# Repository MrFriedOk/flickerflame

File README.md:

# flickerflame
## What

## Why

## References
- [Cloveian](https://github.com/Cloveian)
- ["void_switch"](https://github.com/riskable/void_switch)
- [crkbd](https://github.com/foostan/crkbd)
- [SK9822 symbols/footprints](https://github.com/Crafty-The-Fox/SK9822-EC20-Kicad/tree/main)

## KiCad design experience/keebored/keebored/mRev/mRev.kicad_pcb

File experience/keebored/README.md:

# Keebored (idk what to name it)
## Objective
My goal with this project is to familiarize myself with KiCAD and other CAD-ing tools so I can move towards building a mouse. Not only that, but I can *maybe* get a functional keyboard sort of thing to use to play osu! or something.
## Overview, the idea
A small, semi-portable USB C keyboard.
### Key Features
- 128x64 OLED display via I2C
- Analog HE switches, directly to MCU ADC (hall effect)
- RGB per key
- 1khz (ceiling due to USB restrictions without PHY)
- Rotary encoder
~~- ~55mm wide, ~95mm tall~~
## [Design](./design/README.md)

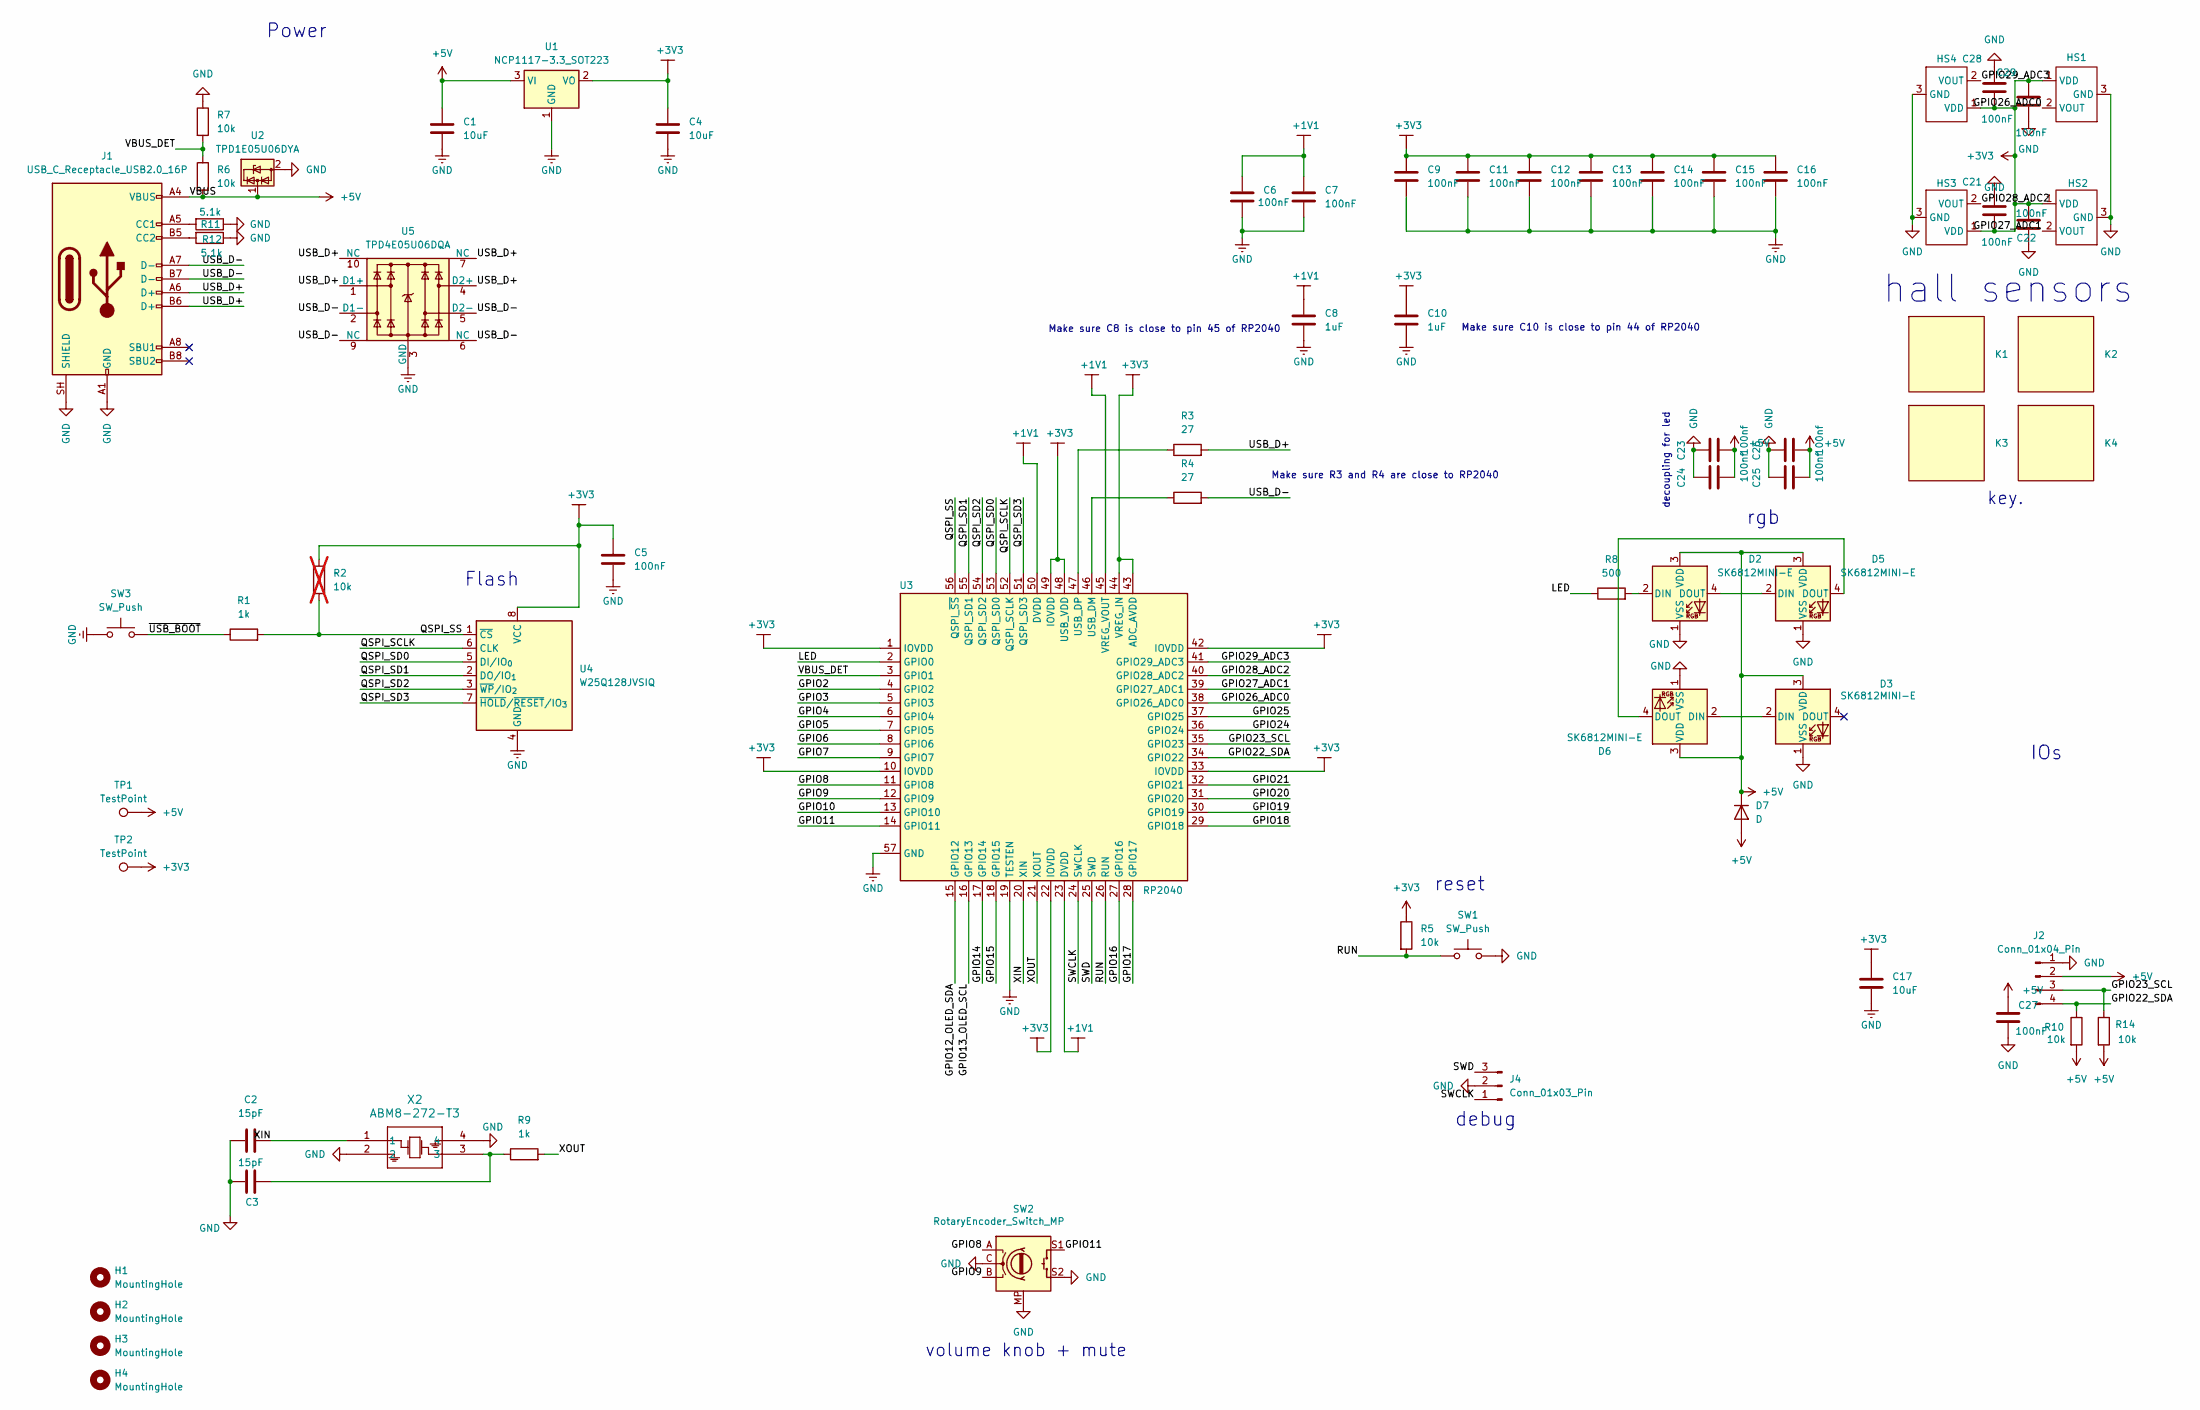
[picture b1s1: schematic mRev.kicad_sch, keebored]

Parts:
C1, C4, C17: 10uF; C_0805_2012Metric
C2, C3: 15pF; C_0402_1005Metric
C5, C6, C7, C9, C11, C12, C13, C14, C15, C16, C21, C22, C27, C28, C29: 100nF; C_0402_1005Metric
C8, C10: 1uF; C_0402_1005Metric
C23, C24, C25, C26: 100nf; C_0402_1005Metric
D2, D3, D5, D6: SK6812MINI-E; LED_SK6812MINI-E_3.2x2.8mm_P1.5mm_ReverseMount
D7: D; D_0402_1005Metric
H1, H2, H3, H4: MountingHole; MountingHole_3mm
HS1, HS2, HS3, HS4: SOT-23-3
J1: USB_C_Receptacle_USB2.0_16P; USB_C_Receptacle_HCTL_HC-TYPE-C-16P-01A
J2: Conn_01x04_Pin; JST_XH_S4B-XH-A-1_1x04_P2.50mm_Horizontal
J4: Conn_01x03_Pin; JST_XH_S3B-XH-A-1_1x03_P2.50mm_Horizontal
K1, K2, K3, K4: HE_Switch_Socket
R1, R9: 1k; R_0402_1005Metric
R2: 10k; R_0402_1005Metric; not fitted
R3, R4: 27; R_0402_1005Metric
R5, R6, R7, R10, R14: 10k; R_0402_1005Metric
R8: 500; R_0402_1005Metric
R11, R12: 5.1k; R_0402_1005Metric
SW1, SW3: SW_Push; SW_PUSH_1P1T_6x3.5mm_H4.3_APEM_MJTP1243
SW2: RotaryEncoder_Switch_MP; RotaryEncoder_Alps_EC11E-Switch_Vertical_H20mm
TP1, TP2: TestPoint; TestPoint_Pad_D1.0mm
U1: NCP1117-3.3_SOT223; SOT-223-3_TabPin2
U2: TPD1E05U06DYA; D_SOD-523
U3: RP2040; QFN-56-1EP_7x7mm_P0.4mm_EP3.2x3.2mm; part_uid RP-01EKHS-ZTKTEH
U4: W25Q128JVSIQ; SOIC-8_5.3x5.3mm_P1.27mm; JLCPCB Part # C113767
U5: TPD4E05U06DQA; USON-10_2.5x1.0mm_P0.5mm
X2: ABM8-272-T3; ABM8-272-T3_ABR

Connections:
+1V1: C6.1, C7.1, C8.1, U3.23 (DVDD), U3.45 (VREG_VOUT), U3.50 (DVDD)
+3V3: C4.1, C5.1, C9.1, C10.1, C11.1, C12.1, C13.1, C14.1, C15.1, C16.1, C17.1, C21.1, C22.1, C28.1, C29.2, HS1.1 (VDD), HS2.1 (VDD), HS3.1 (VDD), HS4.1 (VDD), R2.1, R5.1, TP2.1 (1_1), U1.2 (VO), U3.1 (IOVDD), U3.10 (IOVDD), U3.22 (IOVDD), U3.33 (IOVDD), U3.42 (IOVDD), U3.43 (ADC_AVDD), U3.44 (VREG_IN), U3.48 (USB_VDD), U3.49 (IOVDD), U4.8 (VCC)
+5V: C1.1, C23.2, C24.2, C25.2, C26.2, C27.1, D2.3 (VDD), D3.3 (VDD), D5.3 (VDD), D6.3 (VDD), D7.1 (K), D7.2 (A), J1.A4 (VBUS), J1.A9 (VBUS), J1.B4 (VBUS), J1.B9 (VBUS), J2.2, R6.2, R10.2, R14.2, TP1.1 (1_1), U1.3 (VI), U2.1 (I/O)
/GPIO2: U3.4 (GPIO2)
/GPIO3: U3.5 (GPIO3)
/GPIO4: U3.6 (GPIO4)
/GPIO5: U3.7 (GPIO5)
/GPIO6: U3.8 (GPIO6)
/GPIO7: U3.9 (GPIO7)
/GPIO8: SW2.A, U3.11 (GPIO8)
/GPIO9: SW2.B, U3.12 (GPIO9)
/GPIO10: U3.13 (GPIO10)
/GPIO11: SW2.S1, U3.14 (GPIO11)
/GPIO12_OLED_SDA: U3.15 (GPIO12)
/GPIO13_OLED_SCL: U3.16 (GPIO13)
/GPIO14: U3.17 (GPIO14)
/GPIO15: U3.18 (GPIO15)
/GPIO16: U3.27 (GPIO16)
/GPIO17: U3.28 (GPIO17)
/GPIO18: U3.29 (GPIO18)
/GPIO19: U3.30 (GPIO19)
/GPIO20: U3.31 (GPIO20)
/GPIO21: U3.32 (GPIO21)
/GPIO22_SDA: J2.4, R10.1, U3.34 (GPIO22)
/GPIO23_SCL: J2.3, R14.1, U3.35 (GPIO23)
/GPIO24: U3.36 (GPIO24)
/GPIO25: U3.37 (GPIO25)
/GPIO26_ADC0: HS1.2 (VOUT), U3.38 (GPIO26_ADC0)
/GPIO27_ADC1: HS2.2 (VOUT), U3.39 (GPIO27_ADC1)
/GPIO28_ADC2: HS3.2 (VOUT), U3.40 (GPIO28_ADC2)
/GPIO29_ADC3: HS4.2 (VOUT), U3.41 (GPIO29_ADC3)
/LED: R8.1, U3.2 (GPIO0)
/QSPI_SCLK: U3.52 (QSPI_SCLK), U4.6 (CLK)
/QSPI_SD0: U3.53 (QSPI_SD0), U4.5 (DI/IO_{0})
/QSPI_SD1: U3.55 (QSPI_SD1), U4.2 (DO/IO_{1})
/QSPI_SD2: U3.54 (QSPI_SD2), U4.3 (~WP/IO_{2})
/QSPI_SD3: U3.51 (QSPI_SD3), U4.7 (~HOLD/~RESET/IO_{3})
/QSPI_SS: R1.2, R2.2, U3.56 (QSPI_~SS), U4.1 (~CS)
/RUN: R5.2, SW1.1, U3.26 (RUN)
/SWCLK: J4.1, U3.24 (SWCLK)
/SWD: J4.3, U3.25 (SWD)
/USB_D+: J1.A6 (D+), J1.B6 (D+), R3.2, U5.1 (D1+), U5.4 (D2+), U5.7 (NC), U5.10 (NC)
/USB_D-: J1.A7 (D-), J1.B7 (D-), R4.2, U5.2 (D1-), U5.5 (D2-), U5.6 (NC), U5.9 (NC)
/VBUS_DET: R6.1, R7.2, U3.3 (GPIO1)
/XIN: C2.2, U3.20 (XIN), X2.1
/XOUT: R9.2, U3.21 (XOUT)
/~USB_BOOT: R1.1, SW3.2
GND: C1.2, C2.1, C3.1, C4.2, C5.2, C6.2, C7.2, C8.2, C9.2, C10.2, C11.2, C12.2, C13.2, C14.2, C15.2, C16.2, C17.2, C21.2, C22.2, C23.1, C24.1, C25.1, C26.1, C27.2, C28.2, C29.1, D2.1 (VSS), D3.1 (VSS), D5.1 (VSS), D6.1 (VSS), HS1.3 (GND), HS2.3 (GND), HS3.3 (GND), HS4.3 (GND), J1.A1 (GND), J1.A12 (GND), J1.B1 (GND), J1.B12 (GND), J1.SH (SHIELD), J2.1, J4.2, R7.1, R11.1, R12.1, SW1.2, SW2.C, SW2.MP, SW2.S2, SW3.1, U1.1 (GND), U2.2 (GND), U3.19 (TESTEN), U3.57 (GND), U4.4 (GND), U5.3 (GND), U5.8 (GND), X2.2, X2.4
unnamed: C3.2, R9.1, X2.3
unnamed: D2.2 (DIN), R8.2
unnamed: D2.4 (DOUT), D5.2 (DIN)
unnamed: D3.2 (DIN), D6.2 (DIN)
unnamed: D5.4 (DOUT), D6.4 (DOUT)
unnamed: J1.A5 (CC1), R11.2
unnamed: J1.B5 (CC2), R12.2
unnamed: R4.1, U3.46 (USB_DM)
unnamed: R3.1, U3.47 (USB_DP)

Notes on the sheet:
volume knob + mute
rgb
Power
hall sensors
Flash
reset
IOs
Make sure C10 is close to pin 44 of RP2040
Make sure C8 is close to pin 45 of RP2040
Make sure R3 and R4 are close to RP2040
key.
decoupling for led
debug

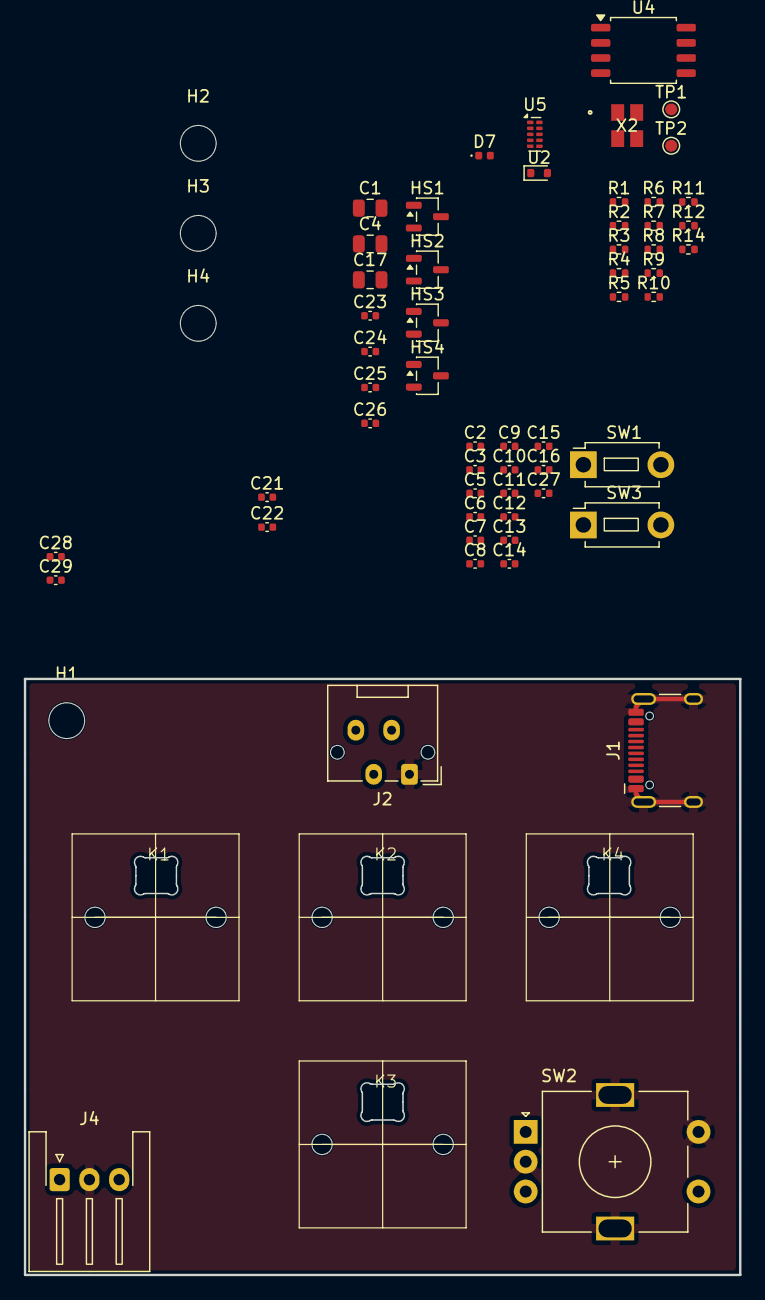
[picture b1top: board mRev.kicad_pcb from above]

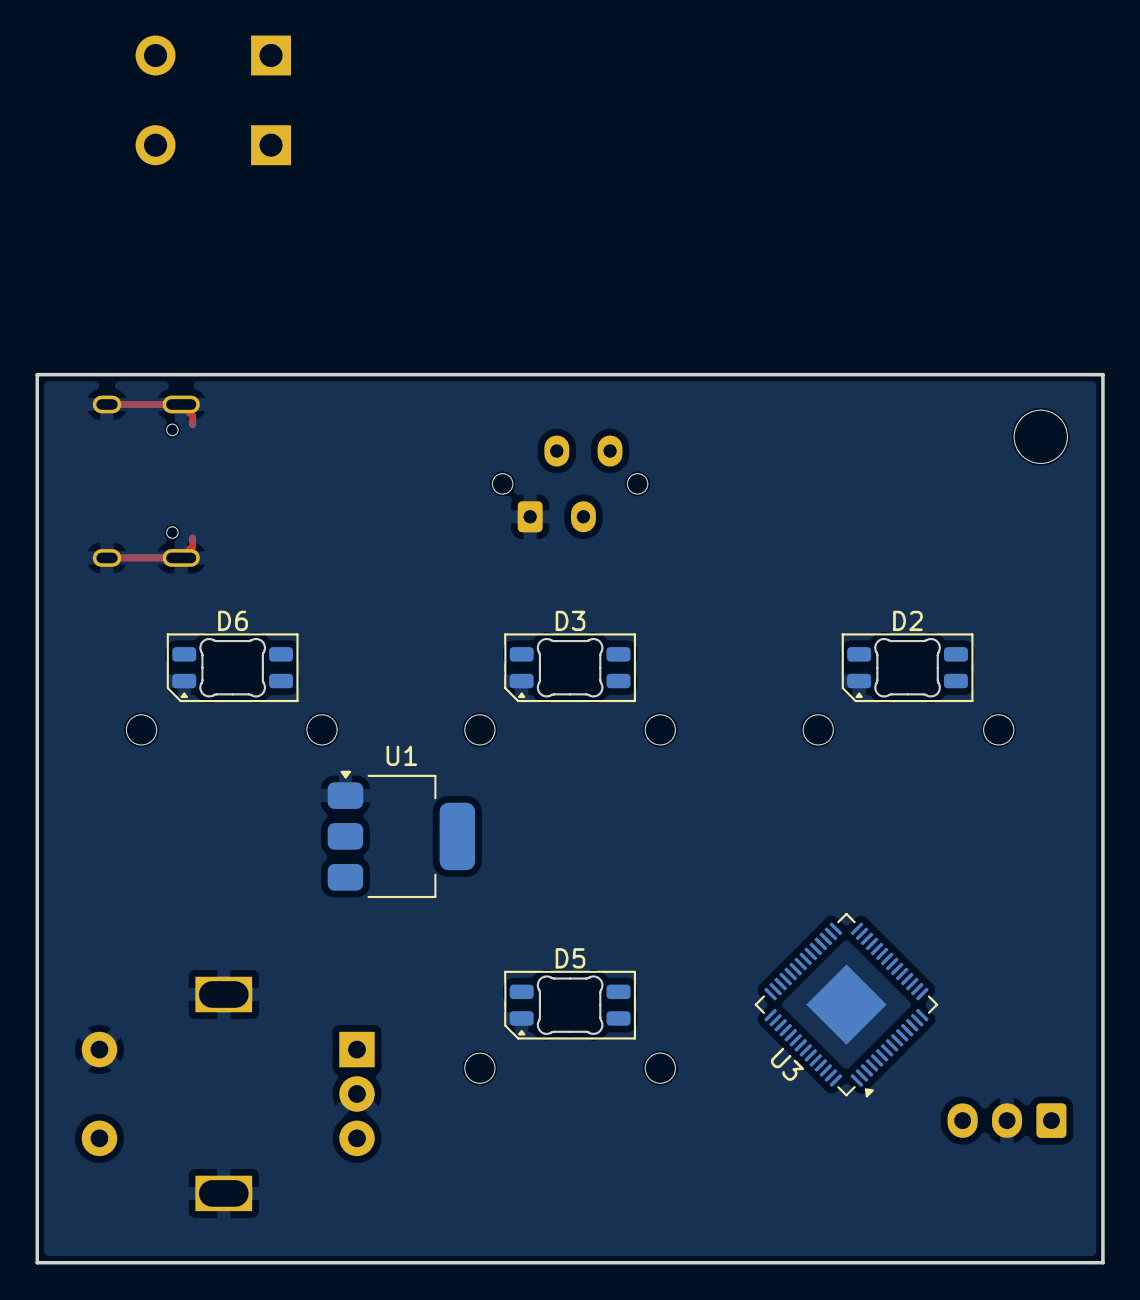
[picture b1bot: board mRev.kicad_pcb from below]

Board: 2 copper layers, 60.0 x 50.0 mm, 70 parts (6 on the bottom side), 38 nets.

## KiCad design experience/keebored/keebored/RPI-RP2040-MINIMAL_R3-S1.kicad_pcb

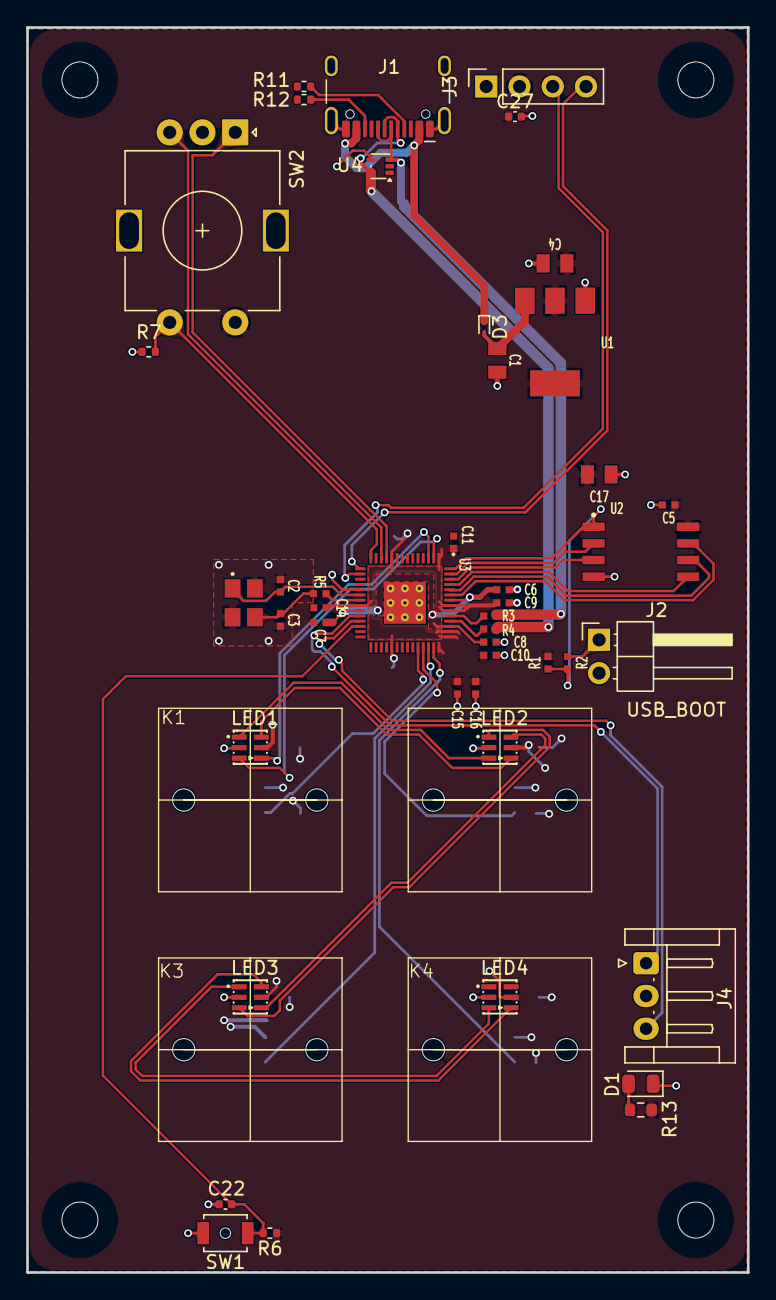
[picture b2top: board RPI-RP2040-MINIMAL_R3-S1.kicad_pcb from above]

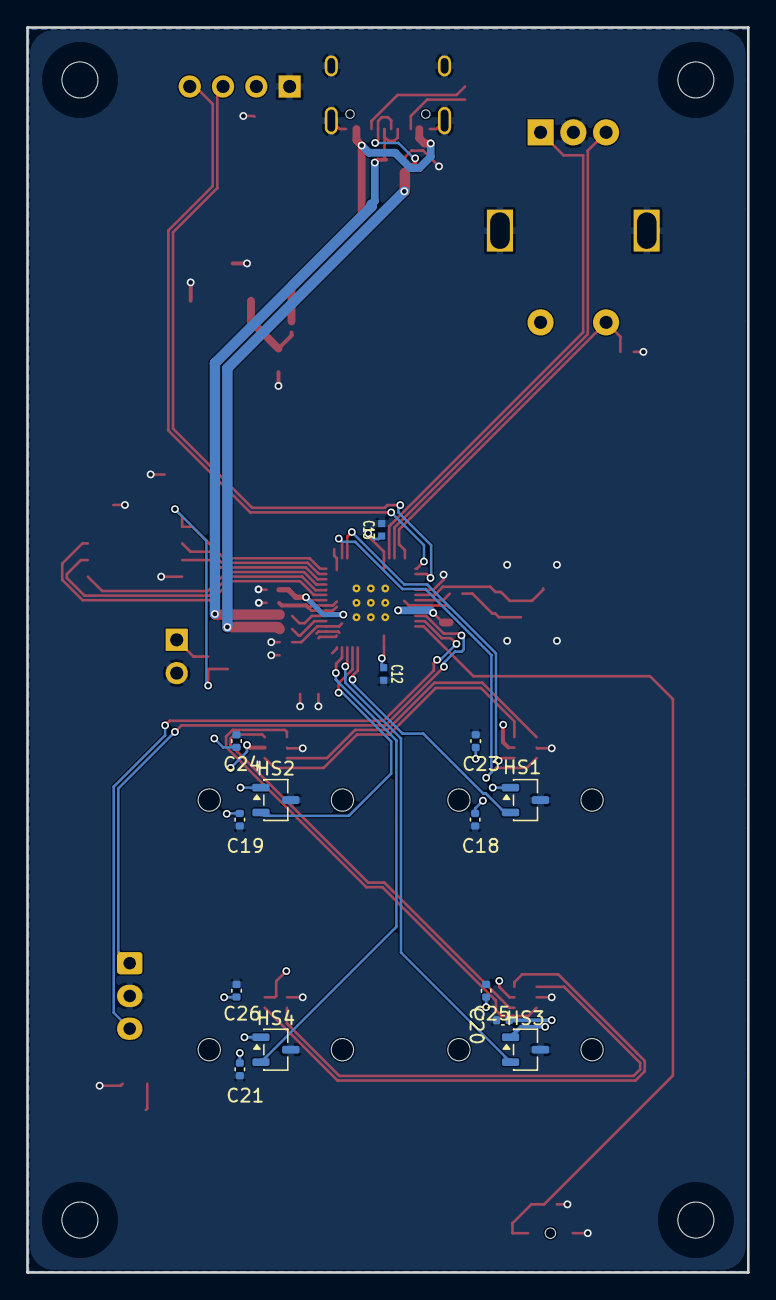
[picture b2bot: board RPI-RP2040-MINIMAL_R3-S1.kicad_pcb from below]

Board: 2 copper layers, 55.0 x 95.0 mm, 66 parts (14 on the bottom side), 42 nets.

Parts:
C1, C4, C17: 10u; generic_capc2012x125
C2, C3: 15p; generic_capc1005x50
C5, C6, C7, C9, C11, C12, C13, C14, C15, C16: 100n; generic_capc1005x50
C8, C10: 1u; generic_capc1005x50
C18, C19, C20, C21, C22, C23, C24, C25, C26, C27: 100nF; C_0402_1005Metric
D1: LED; LED_0805_2012Metric
D3: ESD9B5.0ST5G; D_SOD-923
HS1, HS2, HS3, HS4: SOT-23-3
J1: USB_C_Receptacle_USB2.0_16P; USB_C_Receptacle_HCTL_HC-TYPE-C-16P-01A
J2: TSW-102-07-G-S; PinHeader_1x02_P2.54mm_Horizontal
J3: Conn_01x04_Socket; PinSocket_1x04_P2.54mm_Vertical
J4: Conn_01x03_Pin; JST_EH_S3B-EH_1x03_P2.50mm_Horizontal
K1, K2, K3, K4: HE_Switch_Socket
LED1, LED2, LED3, LED4: SK9822-EC20
MH1, MH2, MH3, MH4: NPTH FD2.75mm SM3.15mm KO6mm; none_mh_npth_fd2p75mm_sm3p15mm_ko6mm
R1, R5: 1k; generic_resc1005x35
R2: 10k; generic_resc1005x35
R3, R4: 27; generic_resc1005x35
R6, R7: 10k; R_0402_1005Metric
R11, R12: 5.1k; R_0402_1005Metric
R13: 100; R_0603_1608Metric
SW1: SW_Push; SW_SPST_B3U-1000P-B
SW2: RotaryEncoder_Switch_MP; RotaryEncoder_Alps_EC11E-Switch_Vertical_H20mm
U1: NCP1117ST33T3G; onsemi_ncp1117st33t3g
U2: W25Q128JVSIQ; generic_soic127p790x195-8
U3: RP2040; rpi_rp2040_vias
U4: TPD2E2U06DRL; SOT-553
X1: 12MHz; generic_xtalcc320x250x80-4

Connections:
+1V1: C6.1, C7.1, C8.1, U3.23 (DVDD), U3.45 (VREG_VOUT), U3.50 (DVDD)
+3V3: C4.1, C5.1, C9.1, C10.1, C11.1, C12.1, C13.1, C14.1, C15.1, C16.1, C17.1, C18.1, C19.1, C20.1, C21.1, C23.2, C24.2, C25.2, C26.2, C27.1, HS1.1 (VDD), HS2.1 (VDD), HS3.1 (VDD), HS4.1 (VDD), J3.2, LED1.5 (VDD), LED2.5 (VDD), LED3.5 (VDD), LED4.5 (VDD), R2.1, R6.1, R13.2, SW2.S2, U1.2 (OUT), U1.4 (OUT), U2.8 (VCC), U3.1 (IOVDD), U3.10 (IOVDD), U3.22 (IOVDD), U3.33 (IOVDD), U3.42 (IOVDD), U3.43 (ADC_AVDD), U3.44 (VREG_IN), U3.48 (USB_VDD), U3.49 (IOVDD)
/GPIO0: LED1.3 (SDI), U3.2 (GPIO0)
/GPIO1: LED1.4 (CKI), U3.3 (GPIO1)
/GPIO8: SW2.A, U3.11 (GPIO8)
/GPIO9: SW2.B, U3.12 (GPIO9)
/GPIO11: R7.1, SW2.S1, U3.14 (GPIO11)
/GPIO12: J3.4, U3.15 (GPIO12)
/GPIO13: J3.3, U3.16 (GPIO13)
/GPIO26_ADC0: HS1.2 (VOUT), U3.38 (GPIO26_ADC0)
/GPIO27_ADC1: HS2.2 (VOUT), U3.39 (GPIO27_ADC1)
/GPIO28_ADC2: HS3.2 (VOUT), U3.40 (GPIO28_ADC2)
/GPIO29_ADC3: HS4.2 (VOUT), U3.41 (GPIO29_ADC3)
/QSPI_SCLK: U2.6 (CLK), U3.52 (QSPI_SCLK)
/QSPI_SD0: U2.5 (DI_IO0), U3.53 (QSPI_SD0)
/QSPI_SD1: U2.2 (DO_IO1), U3.55 (QSPI_SD1)
/QSPI_SD2: U2.3 (~WP_IO2), U3.54 (QSPI_SD2)
/QSPI_SD3: U2.7 (~HOLD_IO3), U3.51 (QSPI_SD3)
/QSPI_SS: R1.1, R2.2, U2.1 (~CS), U3.56 (QSPI_~SS)
/RUN: C22.1, R6.2, SW1.1, U3.26 (RUN)
/SWCLK: J4.1, U3.24 (SWCLK)
/SWD: J4.3, U3.25 (SWD)
/USB_D+: J1.A6 (D+), J1.B6 (D+), R3.1, U4.3
/USB_D-: J1.A7 (D-), J1.B7 (D-), R4.1, U4.5
/VBUS: C1.1, D3.2 (A2), U1.3 (IN)
/XIN: C2.1, U3.20 (XIN), X1.1
/XOUT: R5.2, U3.21 (XOUT)
/~USB_BOOT: J2.1, R1.2
GND: C1.2, C2.2, C3.2, C4.2, C5.2, C6.2, C7.2, C8.2, C9.2, C10.2, C11.2, C12.2, C13.2, C14.2, C15.2, C16.2, C17.2, C18.2, C19.2, C20.2, C21.2, C22.2, C23.1, C24.1, C25.1, C26.1, C27.2, D1.1 (K), HS1.3 (GND), HS2.3 (GND), HS3.3 (GND), HS4.3 (GND), J1.A1 (GND), J1.A12 (GND), J1.B1 (GND), J1.B12 (GND), J1.SH (SHIELD), J2.2, J3.1, J4.2, LED1.2 (GND), LED2.2 (GND), LED3.2 (GND), LED4.2 (GND), R7.2, R11.1, R12.1, SW1.2, SW2.C, SW2.MP, U1.1 (GND), U2.4 (GND), U3.19 (TESTEN), U3.57 (GND), U4.4, X1.2, X1.4
unnamed: C3.1, R5.1, X1.3
unnamed: D1.2 (A), R13.1
unnamed: D3.1 (A1), J1.A4 (VBUS), J1.A9 (VBUS), J1.B4 (VBUS), J1.B9 (VBUS)
unnamed: J1.A5 (CC1), R11.2
unnamed: J1.B5 (CC2), R12.2
unnamed: LED1.6 (CKO), LED2.4 (CKI)
unnamed: LED1.1 (SDO), LED2.3 (SDI)
unnamed: LED2.6 (CKO), LED3.4 (CKI)
unnamed: LED2.1 (SDO), LED3.3 (SDI)
unnamed: LED3.6 (CKO), LED4.4 (CKI)
unnamed: LED3.1 (SDO), LED4.3 (SDI)
unnamed: R4.2, U3.46 (USB_DM)
unnamed: R3.2, U3.47 (USB_DP)

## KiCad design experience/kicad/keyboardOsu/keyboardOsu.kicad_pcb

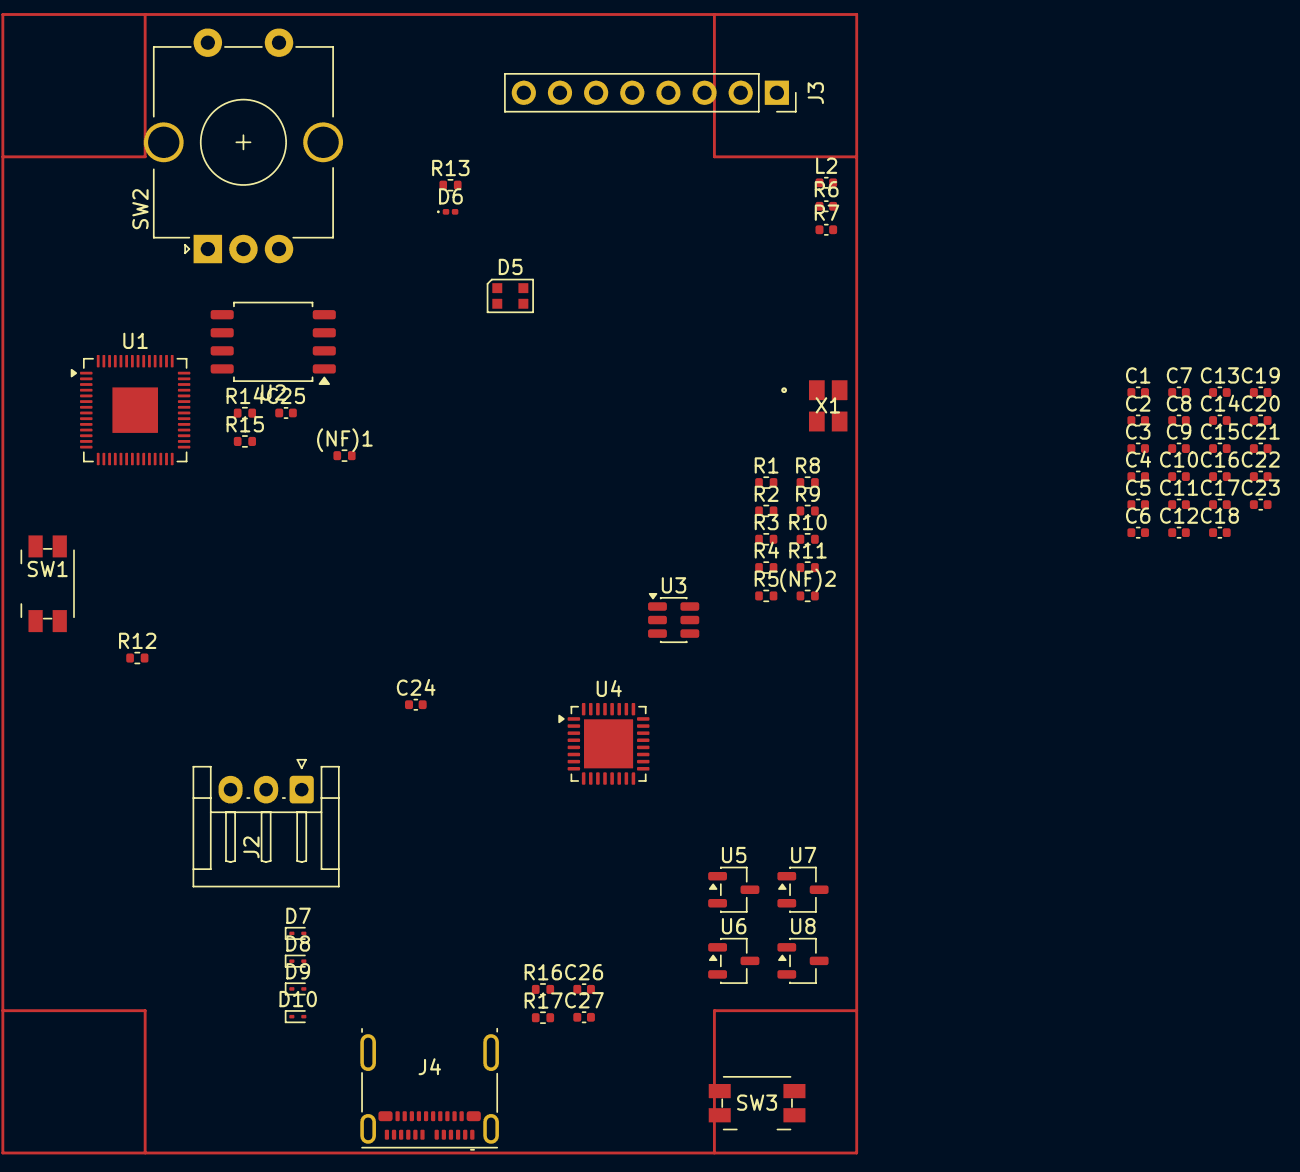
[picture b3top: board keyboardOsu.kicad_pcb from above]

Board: 2 copper layers, 68 parts (0 on the bottom side), 30 nets, no tracks yet.

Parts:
(NF)1, (NF)2: 1M; R_0402_1005Metric
C1, C2, C3, C4, C5, C6, C7, C8, C9, C23, C25: 100nF; C_0402_1005Metric
C10, C11, C12: 2.2uF; C_0402_1005Metric
C13, C14, C26, C27: 1uF; C_0402_1005Metric
C15: 10uF; C_0402_1005Metric
C16, C19: .1uF; C_0402_1005Metric
C17, C18: 22uF; C_0402_1005Metric
C20: 75pF; C_0402_1005Metric
C21, C22: 15pF; C_0402_1005Metric
C24: 0.1uF; C_0402_1005Metric
D5: LED_ARGB; LED_WS2812B-2020_PLCC4_2.0x2.0mm
D6: LED; LED_0201_0603Metric
D7, D8, D9, D10: ESD9B5.0ST5G; D_SOD-923
J2: Conn_01x03_Pin; JST_EH_S3B-EH_1x03_P2.50mm_Horizontal
J3: Conn_01x08_Socket; PinSocket_1x08_P2.54mm_Vertical
J4: USB_C_Receptacle; USB_C_Receptacle_Molex_105450-0101
L2: 10uH; C_0402_1005Metric
R1: 200; R_0402_1005Metric
R2, R5, R16, R17: 5.1k; R_0402_1005Metric
R3, R4, R14: 27; R_0402_1005Metric
R6: 511k; C_0402_1005Metric
R7: 105k; C_0402_1005Metric
R8: 49.9; R_0402_1005Metric
R9: 100k; R_0402_1005Metric
R10: 22k; R_0402_1005Metric
R11, R12, R13: 1k; R_0402_1005Metric
R15: 10k; R_0402_1005Metric
SW1, SW3: SW_Push; Panasonic_EVQPUJ_EVQPUA
SW2: RotaryEncoder; RotaryEncoder_Alps_EC12E-Switch_Vertical_H20mm_CircularMoun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
U1: RP2040; QFN-56-1EP_7x7mm_P0.4mm_EP3.2x3.2mm
U2: W25Q128JVS; SOIC-8_5.3x5.3mm_P1.27mm
U3: TPS54302; SOT-23-6
U4: TLC5947RHB; QFN-32-1EP_5x5mm_P0.5mm_EP3.45x3.45mm
U5, U6, U7, U8: SOT-23-3
X1: ABM8-272-T3; ABM8-272-T3_ABR

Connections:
+3V3: (NF)1.1, C1.1, C2.1, C3.1, C4.1, C5.1, C6.1, C7.1, C11.1, C17.1, C18.1, C23.1, C24.1, J3.6, L2.2, R1.1, R8.1, R13.1, R15.2, U1.1 (IOVDD), U1.10 (IOVDD), U1.22 (IOVDD), U1.33 (IOVDD), U1.42 (IOVDD), U1.44 (VREG_VIN), U1.48 (USB_VDD), U1.49 (IOVDD), U2.8 (VCC), U4.28 (VCC), U5.1 (VDD), U6.1 (VDD), U7.1 (VDD), U8.1 (VDD)
+5V: C13.1, C14.1, C15.1, C16.1, C26.1, C27.1, D7.2 (A2), D8.2 (A2), J4.A4 (VBUS), J4.A9 (VBUS), J4.B4 (VBUS), J4.B9 (VBUS), R6.1, U3.3 (VIN)
GND: C1.2, C2.2, C3.2, C4.2, C5.2, C6.2, C7.2, C8.2, C9.2, C10.2, C11.2, C12.2, C13.2, C14.2, C15.2, C16.2, C17.2, C18.2, C21.1, C22.2, C23.2, C24.2, C25.2, C26.2, C27.2, D6.1 (K), D7.1 (A1), D8.1 (A1), D9.1 (A1), D9.2 (A2), D10.1 (A1), J2.2, J3.8, J4.A1 (GND), J4.A7 (D-), J4.A12 (GND), J4.B1 (GND), J4.B7 (D-), J4.B12 (GND), J4.SH (SHIELD), R2.2, R3.1, R5.2, R7.2, R10.2, R16.2, R17.2, SW1.2, SW3.1, U1.19 (TESTEN), U1.57 (GND), U2.4 (GND), U3.1 (GND), U4.29 (GND), U4.33 (PowerPAD), U5.3 (GND), U6.3 (GND), U7.3 (GND), U8.3 (GND), X1.2, X1.4
unnamed: C20.1, R8.2, R9.1
unnamed: C21.2, R11.1, X1.3
unnamed: D6.2 (A), R13.2
unnamed: D10.2 (A2), J4.A6 (D+), J4.B6 (D+), R4.1
unnamed: J2.1, U1.24 (SWCLK)
unnamed: J2.3, U1.25 (SWDIO)
unnamed: J4.A5 (CC1), R16.1
unnamed: J4.B5 (CC2), R17.1
unnamed: R12.1, SW1.1
unnamed: R14.1, SW3.2
unnamed: C12.1, R1.2, U1.43 (ADC_AVDD)
unnamed: U1.52 (QSPI_SCLK), U2.6 (CLK)
unnamed: U1.53 (QSPI_SD0), U2.5 (DI/IO_{0})
unnamed: U1.55 (QSPI_SD1), U2.2 (DO/IO_{1})
unnamed: U1.54 (QSPI_SD2), U2.3 (~WP/IO_{2})
unnamed: U1.51 (QSPI_SD3), U2.7 (~HOLD/~RESET/IO_{3})
unnamed: C25.1, R14.2, R15.1, U1.26 (RUN)
unnamed: R3.2, U1.46 (USB_DM)
unnamed: R4.2, U1.47 (USB_DP)
unnamed: C8.1, C9.1, C10.1, U1.23 (DVDD), U1.45 (VREG_VOUT), U1.50 (DVDD)
unnamed: (NF)2.1, C22.1, U1.20 (XIN), X1.1
unnamed: (NF)2.2, R11.2, U1.21 (XOUT)
unnamed: (NF)1.2, R12.2, U1.56 (~QSPI_SS), U2.1 (~CS)
unnamed: C19.1, U3.6 (BOOT)
unnamed: R6.2, R7.1, U3.5 (EN)
unnamed: C20.2, R9.2, R10.1, U3.4 (FB)
unnamed: C19.2, L2.1, U3.2 (SW)
